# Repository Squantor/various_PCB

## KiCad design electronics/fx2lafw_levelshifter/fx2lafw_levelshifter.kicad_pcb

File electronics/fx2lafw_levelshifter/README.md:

# FX2 Logicanalyzer level shifter
Level shifter for the cheap FX2 based logic analyzers. Connects to the input port of the LA and requires a 5V supply from the analyzer.
## TODO's
Still some things need to be done:
* schematic entry (Done)
* PCB layout (Done)
* Review with one night in between (Done)
* Produce at [OSHPARK](https://oshpark.com/) (TODO)
* Assemble (TODO)
* Test & characterise (TODO)
* update Readme.md with pictures and BOM (TODO)
## BOM
* [74LVC8T45](https://assets.nexperia.com/documents/data-sheet/74LVC_LVCH8T245.pdf) octal dual supply bidirectional levelshifter

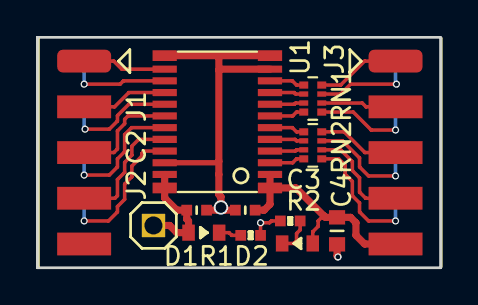
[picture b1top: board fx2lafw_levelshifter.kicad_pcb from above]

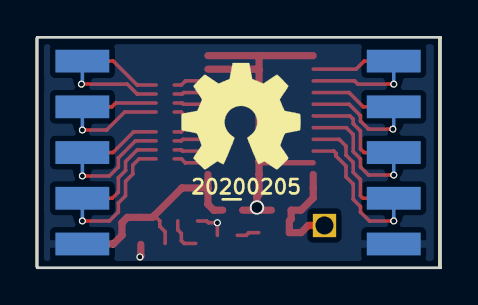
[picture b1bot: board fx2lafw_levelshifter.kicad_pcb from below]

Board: 2 copper layers, 22.4 x 12.8 mm, 15 parts (3 on the bottom side), 29 nets.

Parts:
C2, C3: 1u; C_0402
C4: 10u; C_0603
D1: GREEN; LED_0603_hand
D2: RED; LED_0603_hand
J1: Conn_02x05_Odd_Even; Header-Fem-0254-2X05-SMD-Edge
J2: Conn_01x01; Header-0254-1X01-H010
J3: Conn_02x05_Odd_Even; Header-Male-0254-2X05-SMD-Edge
N1: OHWLOGO; OSHW-Symbol_6.7x6mm_SilkScreen
N2: 20200205; Label_Generic
R1, R2: 1K; R_0402_hand
RN1, RN2: 100; R_Array_Convex_4x0402
U1: 74X8T245; SOT355-1-NXP

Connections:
/CH1: J3.1, RN1.8
/CH1_IN: RN1.1, U1.10
/CH1_OUT: J1.1, U1.14
/CH2: J3.2, RN1.7
/CH2_IN: RN1.2, U1.9
/CH2_OUT: J1.2, U1.15
/CH3: J3.3, RN1.6
/CH3_IN: RN1.3, U1.8
/CH3_OUT: J1.3, U1.16
/CH4: J3.4, RN1.5
/CH4_IN: RN1.4, U1.7
/CH4_OUT: J1.4, U1.17
/CH5: J3.5, RN2.8
/CH5_IN: RN2.1, U1.6
/CH5_OUT: J1.5, U1.18
/CH6: J3.6, RN2.7
/CH6_IN: RN2.2, U1.5
/CH6_OUT: J1.6, U1.19
/CH7: J3.7, RN2.6
/CH7_IN: RN2.3, U1.4
/CH7_OUT: J1.7, U1.20
/CH8: J3.8, RN2.5
/CH8_IN: RN2.4, U1.3
/CH8_OUT: J1.8, U1.21
/VDD_LA: C2.1, D1.2, J2.1, U1.23, U1.24
/VDD_TARGET: C3.1, C4.1, D2.2, J3.9, U1.1, U1.2
/VSS: C2.2, C3.2, C4.2, J1.10, J3.10, R1.2, R2.2, U1.11, U1.12, U1.13, U1.22
unnamed: D1.1, R1.1
unnamed: D2.1, R2.1

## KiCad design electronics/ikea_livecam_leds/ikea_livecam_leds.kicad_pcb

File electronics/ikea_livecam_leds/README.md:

# Ikea Livecam holder LED ring
PCB with LEDS and cross laser powersupply for the Ikea lamp Microsoft Livecam microscope.
## Laser driver
The laser driver consists of a TL431 style constant current sink with a trimpotmeter to adjust the current and thus brightness. Most lasers have a constant current circuit integrated that runs of 5V but this makes it quite bright, overloading the camera in my soldering microscope. 

Values of 4.7K as low side set resistor and 5K trimpot gives a range of 12.5mA to 25.8mA using a shunt resistor of 100Ohm. You can substitute any 1.24V reference TL431 regulator. The TLV431 is used here. A 5V powersupply is also used for lasers that can be driven just by 5V signal, you can then omit the drive circuit and connect the relevant pin to ground.

For the LED series resistors I generally use 3*0805 resistors to spread out the heat a bit. Match to the amount of light you want
# TODO
There are some possible improvements but for now lets use it for a while, here are few improvements I have in mind:
* Change led positions, the inner positions are not useful.
* Move the power distribution trace to the inner side
* Change the series resistor to a dimmable LED driver
* Increase mounting hole size, it fits a 3d print that clamps around something, hole alignment will be a bit off
# BOM
* Osram high CRI LED in 5630 package, OSRAM DURIS
* LM78L05 in SOT89 housing
* TLV431 shunt regulator in SOT23 for laser current control (any 1.24Vref 431 would be suitable)
* Bourns trimpot 3362
# Result
Here is a partially assembled board that was used for tests and characterisation. Fun fact, this board is lit by an webcam that has fully assembled LED ring mounted to it.

I am using 3 parallel 0805 resistors of 150 Ohm to make a 50 Ohm resistor, this limits the current to 70ma at 9V running from a USB-C PD module. This gives plenty of light for my microscope microscope. I am driving my webcam LED's a bit harder with 3 0805 resistors of 120 Ohm to make a 40 Ohm resistor, this is a bit brighter but the leds stay at aroun 50 degrees celcius. They give a ton of light where it matters in front of the camera.

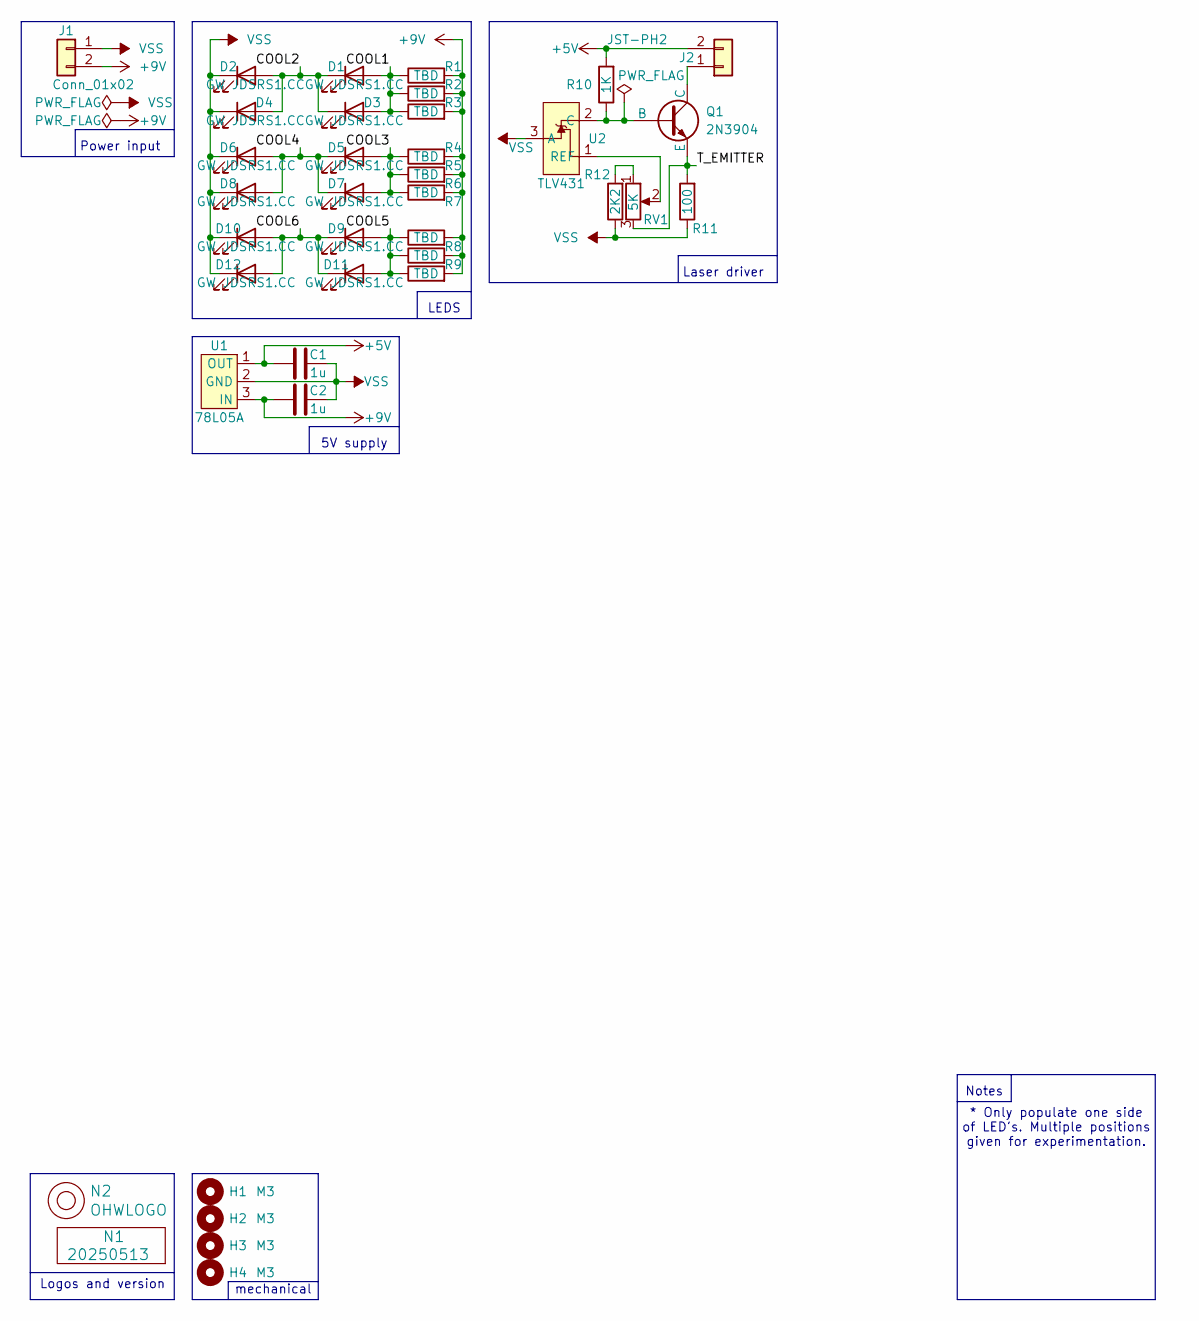
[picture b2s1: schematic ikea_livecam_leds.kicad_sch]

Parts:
C1, C2: 1u; C_0805+0603
D1, D2, D3, D4, D5, D6, D7, D8, D9, D10, D11, D12: GW JDSRS1.CC; LED_5630_PAD_ANODE
H1, H2, H3, H4: M3; MountingHole_3.2mm_M3_Pad_Via
J1: Conn_01x02; JST_XH_S2B-XH-A_1x02_P2.50mm_Horizontal
J2: JST-PH2; JST_PH_S2B-PH-K_1x02_P2.00mm_Horizontal
N1: 20250513; Label_Generic
N2: OHWLOGO; OSHW-Symbol_6.7x6mm_SilkScreen
Q1: 2N3904; SOT23-3
R1, R2, R3, R4, R5, R6, R7, R8, R9: TBD; R_0805+0603
R10: 1K; R_0603_hand
R11: 100; R_0805+0603
R12: 2K2; R_0603_hand
RV1: 5K; POT-Bourns-3362P
U1: 78L05A; SOT89-NXP
U2: TLV431; SOT23-3

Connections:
+5V: C1.1, J2.2, R10.2, U1.1 (OUT)
+9V: C2.1, J1.2, R1.2, R2.2, R3.2, R4.2, R5.2, R6.2, R7.2, R8.2, R9.2, U1.3 (IN)
/COOL1: D1.2 (A), D3.2 (A), R1.1, R2.1, R3.1
/COOL2: D1.1 (K), D2.2 (A), D3.1 (K), D4.2 (A)
/COOL3: D5.2 (A), D7.2 (A), R4.1, R5.1, R6.1
/COOL4: D5.1 (K), D6.2 (A), D7.1 (K), D8.2 (A)
/COOL5: D9.2 (A), D11.2 (A), R7.1, R8.1, R9.1
/COOL6: D9.1 (K), D10.2 (A), D11.1 (K), D12.2 (A)
/T_EMITTER: Q1.3 (E), R11.2, RV1.3
unnamed: J2.1, Q1.1 (C)
unnamed: Q1.2 (B), R10.1, U2.2 (C)
unnamed: R12.2, RV1.1
unnamed: RV1.2, U2.1 (REF)
VSS: C1.2, C2.2, D2.1 (K), D4.1 (K), D6.1 (K), D8.1 (K), D10.1 (K), D12.1 (K), J1.1, R11.1, R12.1, U1.2 (GND), U2.3 (A)

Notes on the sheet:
Notes
LEDS
Logos and version
mechanical
Power input
Laser driver
* Only populate one side of LED's. Multiple positions given for experimentation.
5V supply

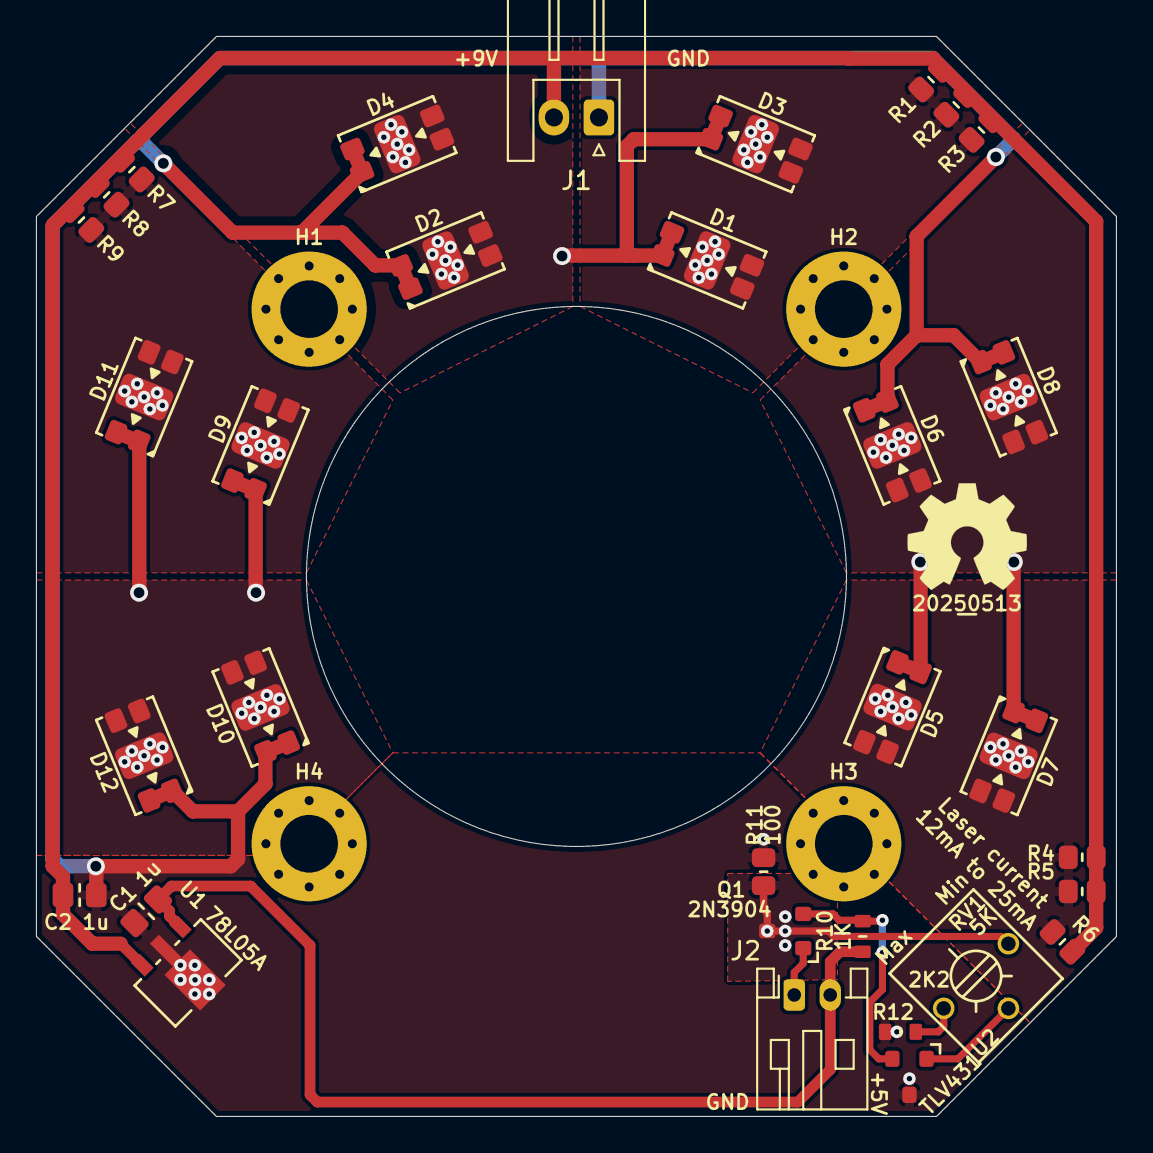
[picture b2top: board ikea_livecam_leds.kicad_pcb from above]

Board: 2 copper layers, 60.0 x 60.0 mm, 38 parts (0 on the bottom side), 14 nets.

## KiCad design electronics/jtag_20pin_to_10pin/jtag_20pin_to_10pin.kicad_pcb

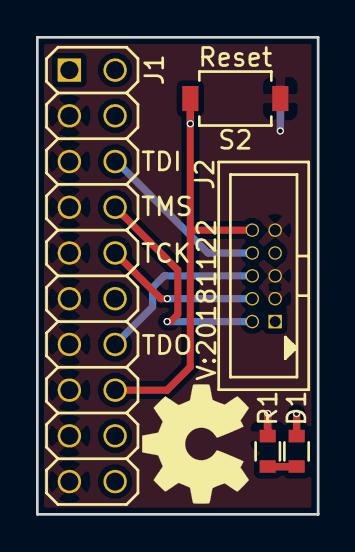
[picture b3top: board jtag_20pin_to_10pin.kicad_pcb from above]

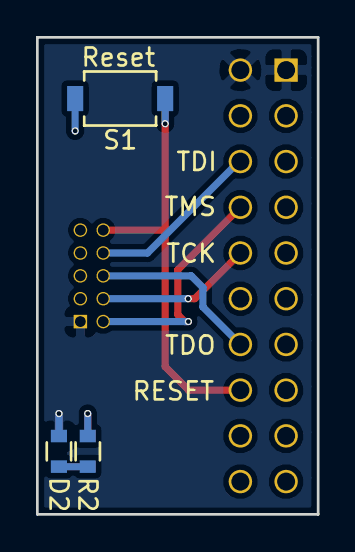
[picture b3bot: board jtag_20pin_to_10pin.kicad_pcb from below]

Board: 2 copper layers, 15.6 x 26.5 mm, 10 parts (3 on the bottom side), 9 nets.

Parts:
D1, D2: LED; R_0603_hand
J1: JTAG_2X10; Header-0245-2X10-H010
J2: JTAG_2X05; Header-Shr-0127-2X05-H006
N1: OHWLOGO; OSHW-Symbol_6.7x6mm_SilkScreen
N2: 20181122; Label_version
R1, R2: R; R_0603_hand
S1, S2: 2pin_tact_switch; TD-85XU

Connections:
/RESET: J1.16, J2.10, S1.1, S2.1
/TCK: J1.10, J2.4
/TDI: J1.6, J2.8
/TDO: J1.14, J2.6
/TMS: J1.8, J2.2
GND: J1.3, J1.5, J1.7, J1.9, J1.11, J1.13, J1.15, J1.17, J1.19, J2.3, J2.5, J2.9, R1.2, R2.2, S1.2, S2.2
unnamed: D1.1, R1.1
unnamed: D2.1, R2.1
VCC: D1.2, D2.2, J1.1, J1.2, J2.1

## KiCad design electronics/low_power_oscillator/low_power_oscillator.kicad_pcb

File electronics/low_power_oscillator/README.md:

# 32KHz low power oscillator experiment
This is a test board for a very low power 32KHz crystal oscillator. Idea from [this](https://www.maximintegrated.com/en/design/technical-documents/app-notes/9/982.html) application note.
## TODO's
* Review with one night in between
* Produce at [OSHPARK](https://oshpark.com/)
* Assemble
* Test & characterise
* update Readme.md with pictures and BOM
## BOM
* [74X1GX04](https://www.lcsc.com/search?q=1gx04) crystal oscillator amplifier.
* [BAS17](https://assets.nexperia.com/documents/data-sheet/BAS17.pdf) stabistor
* [TS431](https://www.st.com/resource/en/datasheet/ts431.pdf) 1.24V shunt regulator
* [MCP6541](https://www.microchip.com/en-us/product/MCP6541) push pull comparator
* [BC849C](https://assets.nexperia.com/documents/data-sheet/BC849_BC850.pdf) NPN BJT transistor with a gain of 100 at 5uA, like the BC849C
# Notes
There is a SOT25/SOT23-5 that can fit a few parts for bias regulation.

* TS431 is a 1.24V shunt regulator but not the lowest power solution, R1 can be used to additionaly bias the regulator if the oscillator does not provide enough bias current.
* Instead of a proper shunt regulator you can also fit a BAV99 double diode there, it is a bit more drifty but probably needs lower bias. It also has a 1.4/1.5V forward voltage in this application.
* BAS17 stabistor is a diode made for be the opposite of the VBE drift, but can also be used as a very low voltage shunt regulator

There are two methods of amplifying the oscillator signal.
* As per application note a comparator is used to compare the bias voltage with the oscillator output
* Another option would be to use unbuffered logic gates, but I expect that these consume a lot of power.

# Measurements
The following configurations will be tried out:

* TS431 with 74LVC1GX04
* TS431 with MCP6541
* BAV99 double diode with MCP6541
* BAV99 single diode with MCP6541
* BAS17 with MCP6541

A few transistors will be tried out, the low noise and very high gain of the BC849C is probably overkill and a BC847B or even A would suffice.

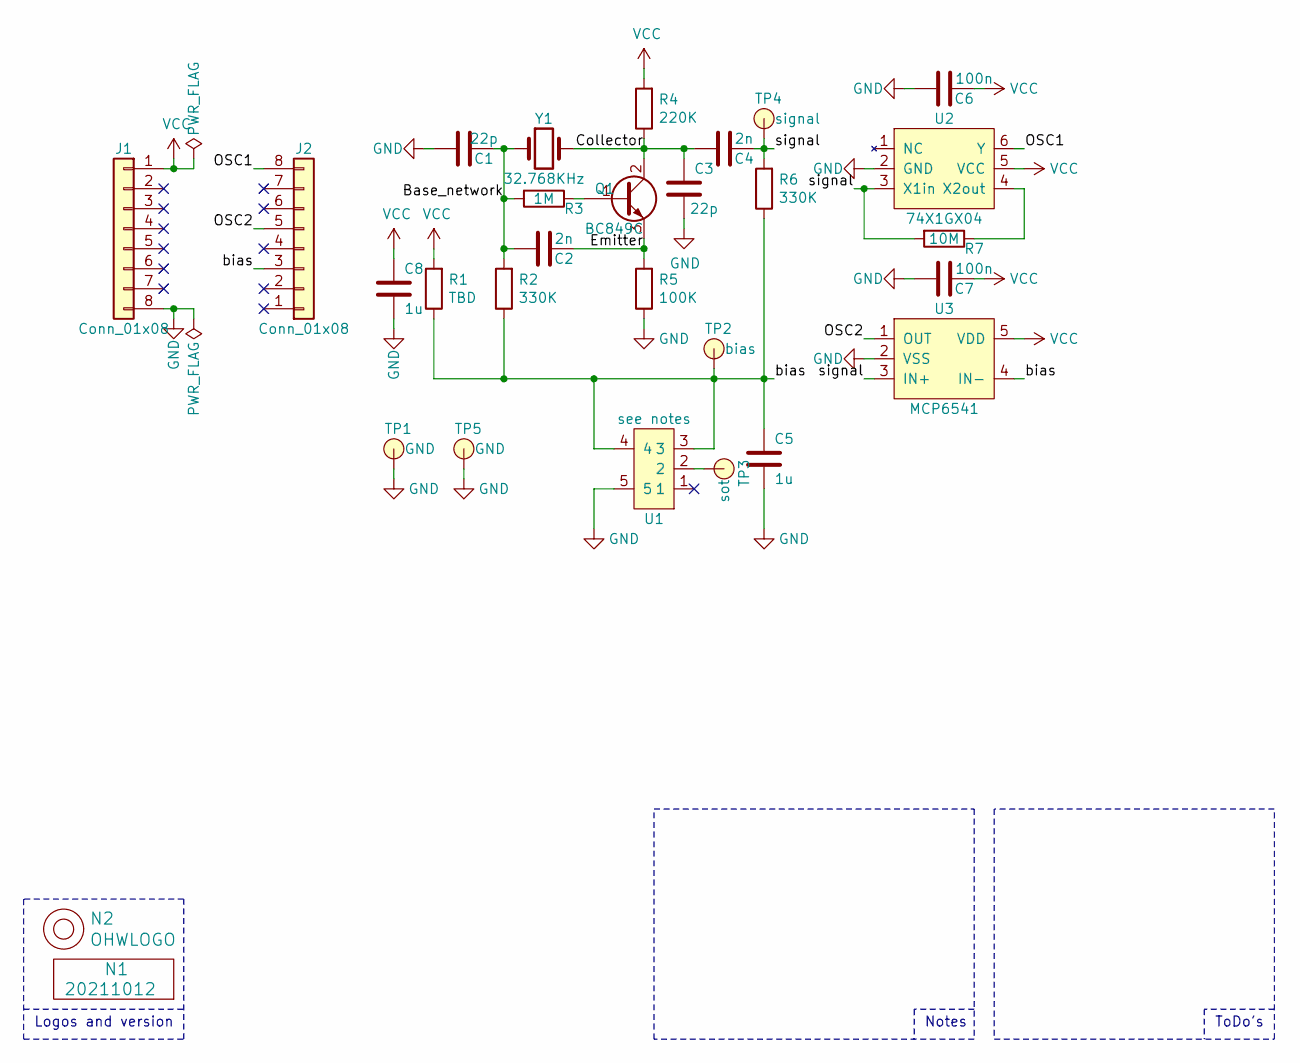
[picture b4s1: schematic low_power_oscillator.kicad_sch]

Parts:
C1, C3: 22p; C_0402
C2, C4: 2n; C_0402
C5, C8: 1u; C_0402
C6, C7: 100n; C_0402
J1, J2: Conn_01x08; Header-0254-1X08-H008
N1: 20211012; Label_Generic
N2: OHWLOGO; OSHW-Symbol_6.7x6mm_SilkScreen
Q1: BC849C; SOT_universal
R1: TBD; R_0402_hand
R2, R6: 330K; R_0402_hand
R3: 1M; R_0402_hand
R4: 220K; R_0402_hand
R5: 100K; R_0402_hand
R7: 10M; R_0402_hand
TP1, TP5: GND; TestPoint_hole_H05R10
TP2: bias; TestPoint_hole_H05R10
TP3: sot; TestPoint_hole_H05R10
TP4: signal; TestPoint_hole_H05R10
U1: see notes; SOT23-5-Microchip-OT
U2: 74X1GX04; SOT363-NXP-hand
U3: MCP6541; SOT23-5-Microchip-OT
Y1: 32.768KHz; Crystal_3215_2

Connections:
/Base_network: C1.1, C2.2, R2.2, R3.2, Y1.1
/Collector: C3.2, C4.2, Q1.2 (C), R4.1, Y1.2
/Emitter: C2.1, Q1.3 (E), R5.2
/OSC1: J2.8, U2.6 (Y)
/OSC2: J2.5, U3.1 (OUT)
/bias: C5.2, J2.3, R1.1, R2.1, R6.1, TP2.1, U1.3, U1.4, U3.4 (IN-)
/signal: C4.1, R6.2, R7.2, TP4.1, U2.3 (X1in), U3.3 (IN+)
GND: C1.2, C3.1, C5.1, C6.2, C7.2, C8.1, J1.8, R5.1, TP1.1, TP5.1, U1.5, U2.2 (GND), U3.2 (VSS)
unnamed: Q1.1 (B), R3.1
unnamed: TP3.1, U1.2
unnamed: R7.1, U2.4 (X2out)
VCC: C6.1, C7.1, C8.2, J1.1, R1.2, R4.2, U2.5 (VCC), U3.5 (VDD)

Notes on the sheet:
Notes
Logos and version
ToDo's

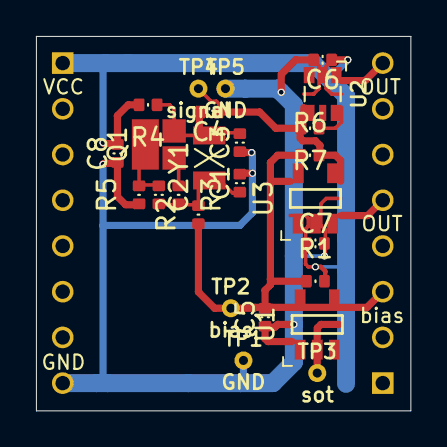
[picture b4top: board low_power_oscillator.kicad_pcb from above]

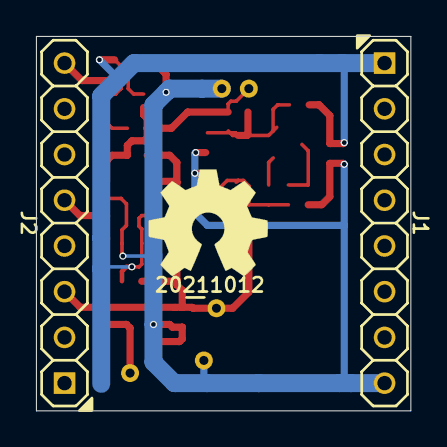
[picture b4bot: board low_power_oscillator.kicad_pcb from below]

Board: 2 copper layers, 20.8 x 20.8 mm, 29 parts (4 on the bottom side), 12 nets.

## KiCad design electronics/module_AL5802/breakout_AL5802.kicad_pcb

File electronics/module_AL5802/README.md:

# AL5802 constant current source breakout
Small breakout board for the AL5802 constant current source.
## TODO's
Still some things need to be done:
* Review with one night in between
* Produce at [OSHPARK](https://oshpark.com/)
* Assemble
* Test & characterise
* update Readme.md with pictures and BOM
## BOM
This is a list of hardware components. If just mentioned a generic component like a 1K 0402 resistor, just name it as such, free to substitute. If you need some special integrated IC's show some sources like Mouser, Digikey, Farnell, or LCSC
* [AL5802](https://lcsc.com/product-detail/LED-Drivers_Diodes-Incorporated-AL5802-7_C129160.html)

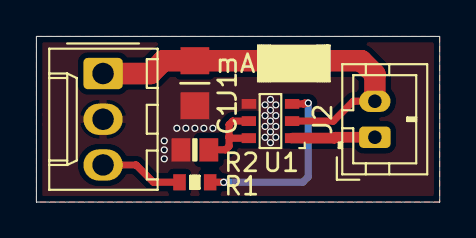
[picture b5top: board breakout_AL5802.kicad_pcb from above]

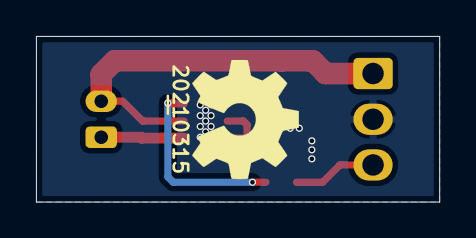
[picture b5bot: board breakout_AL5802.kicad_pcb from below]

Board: 2 copper layers, 22.4 x 9.2 mm, 9 parts (2 on the bottom side), 6 nets.

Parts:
C1: 10u; C_1206_0805
J1: Conn_01x03; Molex_KK-254_AE-6410-03A_1x03_P2.54mm_Vertical
J2: Conn_01x02; JST_PH_B2B-PH-K_1x02_P2.00mm_Vertical
N1: 20210315; Label_Generic
N2: OHWLOGO; OSHW-Symbol_6.7x6mm_SilkScreen
N3: mA:; Label_Note_small
R1: 100; R_0603_hand
R2: FB; R_0805+0603
U1: AL5802; SOT26-diodesinc

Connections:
/Ctrl: J1.3, R1.2
/FB: R2.2, U1.5, U1.6
/GND: C1.1, J1.2, R2.1, U1.4
/LEDI: J2.1, U1.1
/Vin: C1.2, J1.1, J2.2, U1.2
unnamed: R1.1, U1.3

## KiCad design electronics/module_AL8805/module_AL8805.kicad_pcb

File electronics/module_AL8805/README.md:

# AL8805 constant current LED driver module
Small test module for the AL8805 constant current LED driver
## TODO's
Still some things need to be done:
* schematic entry 
* PCB layout
* Review with one night in between
* Produce at [OSHPARK](https://oshpark.com/)
* Assemble
* Test & characterise
* update Readme.md with pictures and BOM
## BOM
* [AL8805](https://lcsc.com/product-detail/LED-Drivers_DIODES_AL8805W5-7_AL8805W5-7_C127927.html)

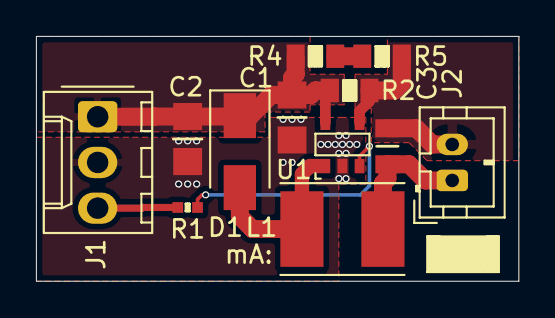
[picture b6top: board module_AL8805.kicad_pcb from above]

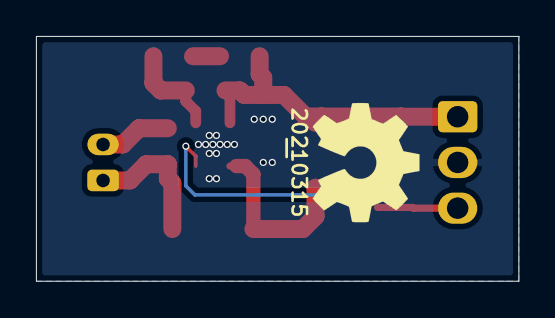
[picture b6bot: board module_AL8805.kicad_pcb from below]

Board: 2 copper layers, 26.8 x 13.6 mm, 15 parts (2 on the bottom side), 8 nets.

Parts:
C1, C2: 10u; C_1206_0805
C3: 1u; C_0805
D1: B240; D_SMA
J1: Conn_01x03; Molex_KK-254_AE-6410-03A_1x03_P2.54mm_Vertical
J2: Conn_01x02; JST_PH_B2B-PH-K_1x02_P2.00mm_Vertical
L1: 33u; L_Taiyo-Yuden_NR-50xx_HandSoldering
N1: 20210315; Label_Generic
N2: OHWLOGO; OSHW-Symbol_6.7x6mm_SilkScreen
N3: mA:; Label_Note_small
R1: 100; R_0402_hand
R2, R4, R5: TBD; R_0805_hand
U1: AL8805; SOT25-diodesinc

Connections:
/Ctrl: J1.3, R1.2
/GND: C1.2, C2.2, J1.2, U1.2
/LED+: C3.1, J2.2, R2.2, R5.2, U1.4
/LED-: C3.2, J2.1, L1.1
/SW: D1.2, L1.2, U1.1
/Vin: C1.1, C2.1, D1.1, J1.1, R2.1, R4.2, U1.5
unnamed: R1.1, U1.3
unnamed: R4.1, R5.1

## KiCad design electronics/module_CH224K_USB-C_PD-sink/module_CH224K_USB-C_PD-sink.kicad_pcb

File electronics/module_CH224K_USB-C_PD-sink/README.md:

# CH224K USB PD sink module
USB PD sink based on CH224K chip. Similar to many aliexpress boards but contains a power good indicator and power good power on switch to switch on power when negotation has completed.
## TODO's
Still some things need to be done:
* schematic entry (WIP)
* PCB layout (WIP)
* Review with one night in between
* Produce
* Assemble
* Test & characterise
* update Readme.md with pictures and BOM
## BOM
* [CH224K](https://www.wch-ic.com/products/CH224.html) from LCSC or Aliexpress
* SOT-23 P channel fet
* 8V zener in SOD323 for Pchannel switch protection

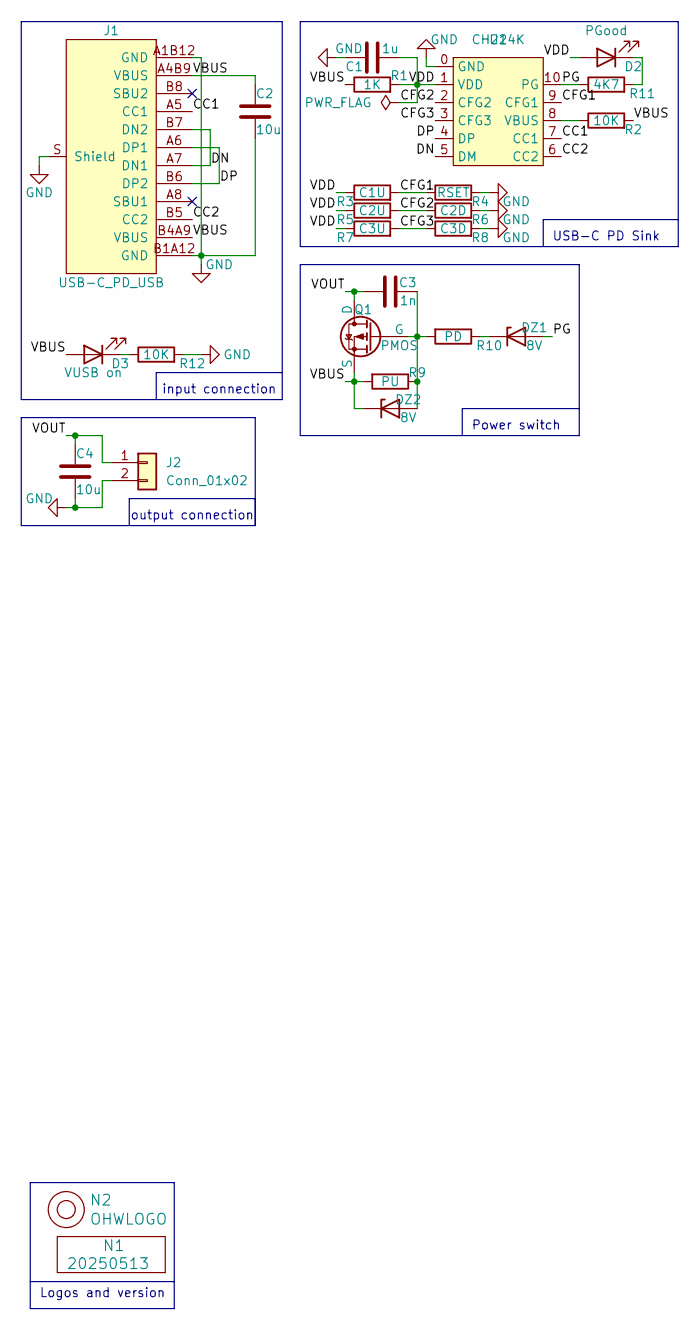
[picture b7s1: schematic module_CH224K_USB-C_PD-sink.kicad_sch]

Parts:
C1: 1u; C_0805+0603
C2, C4: 10u; C_1206_0805
C3: 1n; C_0603
D2: PGood; LED_0603_hand
D3: VUSB on; LED_0603_hand
DZ1, DZ2: 8V; SOD-323-nexperia-hand
J1: USB-C_PD_USB; USB-C-HRO-31-M-12_aisler
J2: Conn_01x02; JST_XH_S2B-XH-A-1_1x02_P2.50mm_Horizontal
N1: 20250513; Label_Generic
N2: OHWLOGO; OSHW-Symbol_6.7x6mm_SilkScreen
Q1: PMOS; SOT23-3
R1: 1K; R_0603_hand
R2, R12: 10K; R_0603_hand
R3: C1U; R_0603_hand
R4: RSET; R_0603_hand
R5: C2U; R_0603_hand
R6: C2D; R_0603_hand
R7: C3U; R_0603_hand
R8: C3D; R_0603_hand
R9: PU; R_0603_hand
R10: PD; R_0603_hand
R11: 4K7; R_0603_hand
U1: CH224K; SSOP-10-1EP_WCH

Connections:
/CC1: J1.A5 (CC1), U1.7 (CC1)
/CC2: J1.B5 (CC2), U1.6 (CC2)
/CFG1: R3.2, R4.1, U1.9 (CFG1)
/CFG2: R5.2, R6.1, U1.2 (CFG2)
/CFG3: R7.2, R8.1, U1.3 (CFG3)
/DN: J1.A7 (DN1), J1.B7 (DN2), U1.5 (DM)
/DP: J1.A6 (DP1), J1.B6 (DP2), U1.4 (DP)
/PG: DZ1.2 (A), R11.1, U1.10 (PG)
/VBUS: C2.1, D3.2 (A), DZ2.1 (K), J1.A4B9 (VBUS), J1.B4A9 (VBUS), Q1.3 (S), R1.1, R2.2, R9.2
/VDD: C1.2, D2.2 (A), R1.2, R3.1, R5.1, R7.1, U1.1 (VDD)
/VOUT: C3.1, C4.1, J2.1, Q1.1 (D)
GND: C1.1, C2.2, C4.2, J1.A1B12 (GND), J1.B1A12 (GND), J1.S (Shield), J2.2, R4.2, R6.2, R8.2, R12.2, U1.0 (GND)
unnamed: D2.1 (K), R11.2
unnamed: D3.1 (K), R12.1
unnamed: DZ1.1 (K), R10.1
unnamed: C3.2, DZ2.2 (A), Q1.2 (G), R9.1, R10.2
unnamed: R2.1, U1.8 (VBUS)

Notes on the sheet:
input connection
Logos and version
output connection
USB-C PD Sink
Power switch

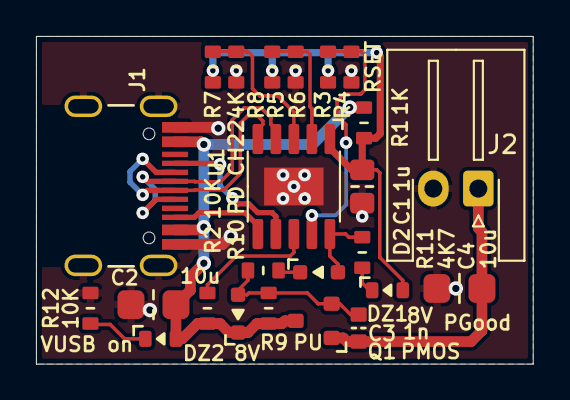
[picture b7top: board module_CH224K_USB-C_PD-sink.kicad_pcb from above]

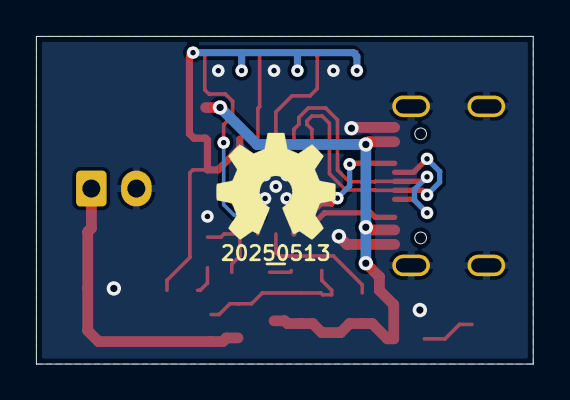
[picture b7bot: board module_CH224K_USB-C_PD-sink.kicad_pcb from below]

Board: 2 copper layers, 27.6 x 18.2 mm, 26 parts (2 on the bottom side), 17 nets.
